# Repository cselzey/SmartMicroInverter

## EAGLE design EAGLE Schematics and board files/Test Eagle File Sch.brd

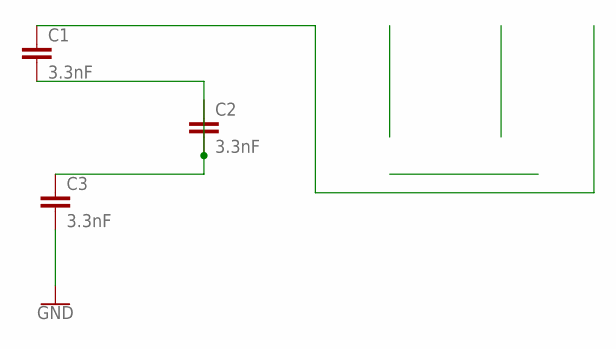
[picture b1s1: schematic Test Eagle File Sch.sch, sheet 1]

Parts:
C1, C2, C3: 3.3nF; 0603

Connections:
GND: C3.2; also elsewhere on the board
unnamed: C1.2, C2.2, C3.1

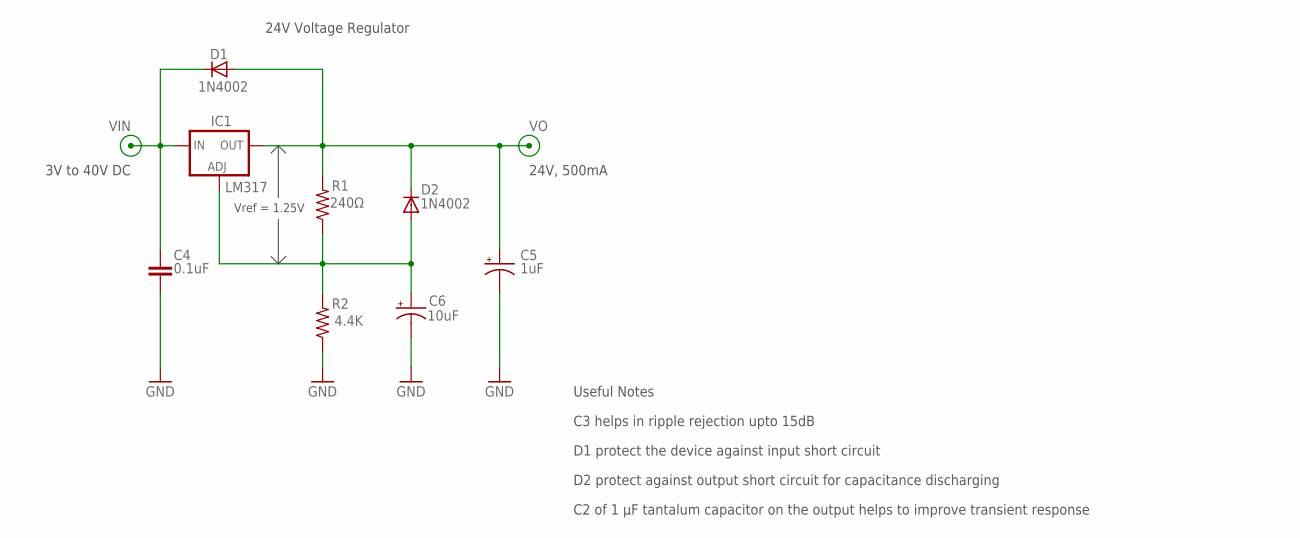
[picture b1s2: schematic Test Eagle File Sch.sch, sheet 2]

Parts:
C4: 0.1uF; C075-052X106
C5: 1uF; 085CS_1AR
C6: 10uF; 085CS_1AR
D1, D2: 1N4002; DO41-10
IC1: LM317MBSTT3; SOT223; PARTNUMBER LM317
R1: 240Ω; M0805
R2: 4.4K; M0805

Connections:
GND: C4.2, C5.-, C6.-, R2.1; also elsewhere on the board
unnamed: C6.+, D2.A, IC1.1 (ADJ), R1.1, R2.2
VIN: C4.1, D1.C, IC1.3 (IN)
VO: C5.+, D1.A, D2.C, IC1.4 (OUT), R1.2

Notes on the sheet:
24V Voltage Regulator
C3 helps in ripple rejection upto 15dB
D1 protect the device against input short circuit
D2 protect against output short circuit for capacitance discharging
C2 of 1 µF tantalum capacitor on the output helps to improve transient response
Useful Notes
24V, 500mA
Vref = 1.25V
3V to 40V DC

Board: 2 copper layers, 11 parts (0 on the bottom side), 5 nets, no tracks yet.

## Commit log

2018-09-24 First Commit
    WOO!
2018-09-26 Add files via upload
    Initial Model for DC-DC section, no transformer. WIP
2018-09-27 Add files via upload
    Updated parameter values for components from paper
2018-10-02 Add files via upload
    Tried slightly different topology, didnt work for a while.
    Adjusted magnetization resistance on transformer and it has actual voltage on both sides now.
    Will need to adjust on main model to see if this was the problem.
2018-10-03 Add files via upload
    Fixed Voltage for paper topology.
    To do:
    Fix issue with drop in power.
    Get waveforms to look like those in paper
2018-10-03 Add files via upload
    There is power on the output.
2018-10-03 Add files via upload
    Modified Duty Cycle for Efficiency. Still need to confirm waveforms to those in paper and implement control block for duty cycle input.
2018-10-03 Add files via upload
    Used actual simulink tools instead of simscape
2018-10-03 Add files via upload
    Functional AC Inverter
2018-10-04 Add files via upload
    Named all the components and put in the correct Rs-On values for S1 and S2
2018-10-04 Add files via upload
    Initial Combination of DC/DC and DC/AC sections.
    No MPPT has been implemented.
    Waveform still not complete sine wave.
2018-10-05 Add files via upload
    Added working inverter with sexy 60 Hz sine-wave
2018-10-20 Add files via upload
    Cleaned up the working pv system with inverter
2018-10-25 Add files via upload
    with our actual PV values
2018-10-25 Add files via upload
    Working? inverter with grid and new component values. Grid current still out of phase
2018-10-25 Add files via upload
    with inductors in the inverter stage (same as paper)
2018-10-27 Added folders
    Added folder for schematics and code
2018-10-28 Add files via upload
    Functioning MPPT Integration with the DC-DC Converter. This is with a load of 695 ohms, allowing the PV module power to get to 358 W, but only allows the output power across the load of 280 W. This r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
2018-10-28 Added test EAGLE doc
2018-10-28 Things changed lol
2018-10-28 Derp Derp :)
    Derp Derp
2018-10-31 Add files via upload
    Microinverter has DC/DC link control implemented.
    Still working on DC/AC circuit and control.
2018-11-01 Add files via upload
    Updated DC link controller with PI block, now goes to correct DC link voltage (as long as the load resistance is not too low)
2018-11-02 Add files via upload
    Tested DC/DC alone, can handle 0.85A current draw and still maintain 350V at DC link.
    AC grid could be causing grid current to be inaccurate (negative since AC grid is supplying current).
    Not sure how to prevent overdrawing power by inverter from converter stage.
2018-11-06 Inverter that produces a good sine wave
2018-11-08 Add files via upload
    ITS <U><B>ACTUALLY</U></B> WORKING
2018-11-11 MQP Values & Cleaned Up
2018-11-11 Add files via upload
    calculated LCL values, current still looks wonky. tried messing around with PI values to no avail
2018-11-15 Polished Microinverter Simulink File
    Just took away all the irrelevant block names and cleaned the lines up with some GoTo's and Froms.
2018-11-16 Updated on 16NOV18
    Updated Converter Switching Characteristics, Updated Rectifier Diode Parameters
2018-11-30 MPPT delay time changed to 0.1
2018-12-02 PI Values
    Decreased the P and I values, while keeping the same ratio. For example for the first PI controller we had a P value of 1 and a I value of 20 giving us a ratio of 200. I decreased it to have a P valu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
2018-12-03 Add files via upload
    Updated inverter values with BOM components
2018-12-03 Add files via upload
    Inverter components are good. Need to find boost components
2018-12-04 Most Up To Date!
    Everything should be the most practical we can get it..
2018-12-07 Final Version
    Only thing that will change from here on out is the irradiance and temperature going into the pv module. Hopefully..
2018-12-12 Dampening Resistor Update
    Updated measurements for voltage and current for the damping resistor coming off the capacitor in the LCL grid filter

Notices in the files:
parts and their libraries:
SparkFun-Capacitors: Licensing: Creative Commons ShareAlike 4.0 International - https://creativecommons.org/licenses/by-sa/4.0
